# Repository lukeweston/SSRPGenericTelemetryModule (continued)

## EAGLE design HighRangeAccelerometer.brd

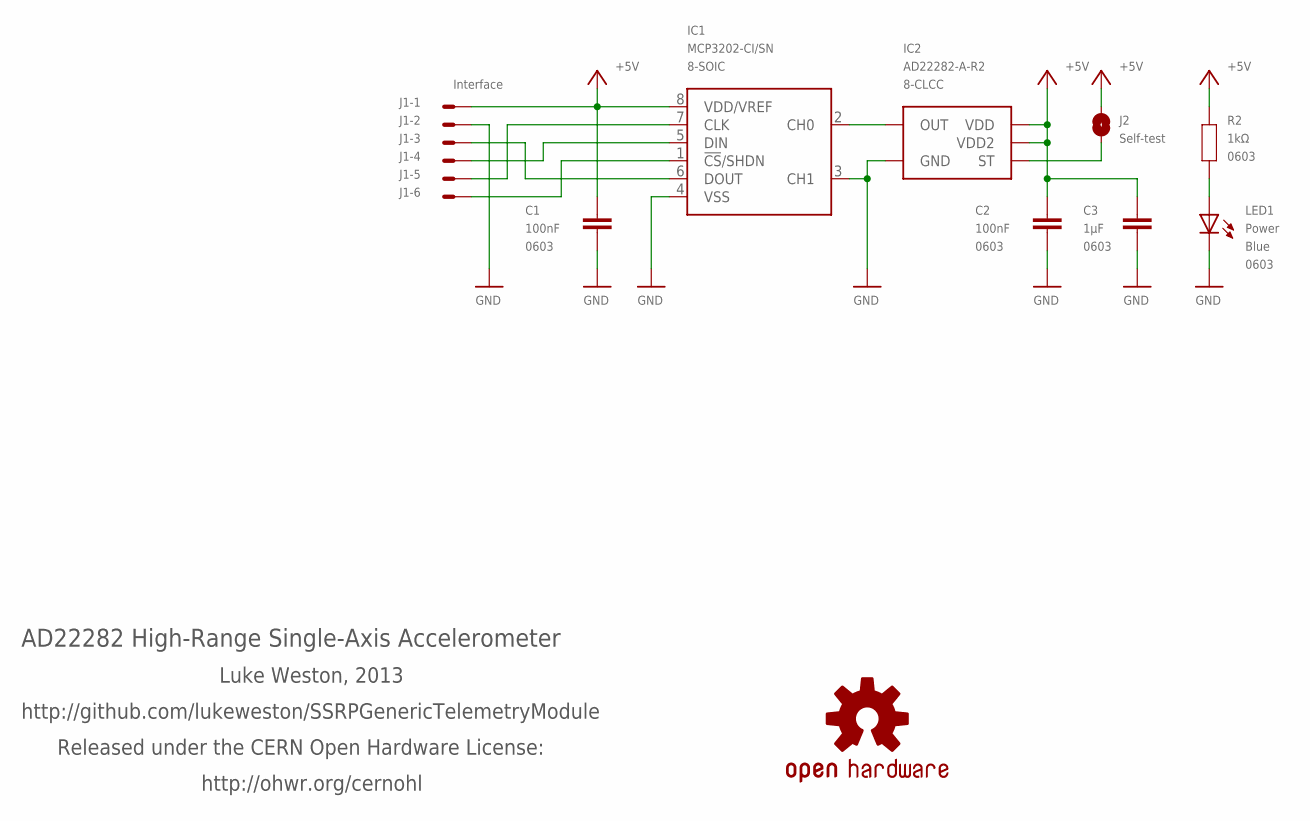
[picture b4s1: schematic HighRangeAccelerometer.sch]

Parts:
C1, C2: 100nF; 0603
C3: 1µF; 0603
IC1: MCP3202-CI/SN; SO-08
IC2: AD22282-A-R2; ADXL193
J1: Interface; 7395-06
J2: Self-test; SJ
LED1: Power; LED-0603
R2: 1kΩ; 0603
SY: OSHW-LOGOS; OSHW-LOGO-S

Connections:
+5V: C1.2, C2.2, C3.2, IC1.8 (VDD/VREF), IC2.P$7 (VDD), IC2.P$8 (VDD2), J1.1, J2.2, R2.2
GND: C1.1, C2.1, C3.1, IC1.3 (CH1), IC1.4 (VSS), IC2.P$3 (GND), J1.2, LED1.C
unnamed: IC1.2 (CH0), IC2.P$6 (OUT)
unnamed: LED1.A, R2.1
unnamed: IC1.6 (DOUT), J1.3
unnamed: IC1.5 (DIN), J1.4
unnamed: IC1.7 (CLK), J1.5
unnamed: IC1.1 (!CS!/SHDN), J1.6
unnamed: IC2.P$4 (ST), J2.1

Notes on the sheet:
AD22282 High-Range Single-Axis Accelerometer
Luke Weston, 2013
http://github.com/lukeweston/SSRPGenericTelemetryModule
Released under the CERN Open Hardware License:
http://ohwr.org/cernohl

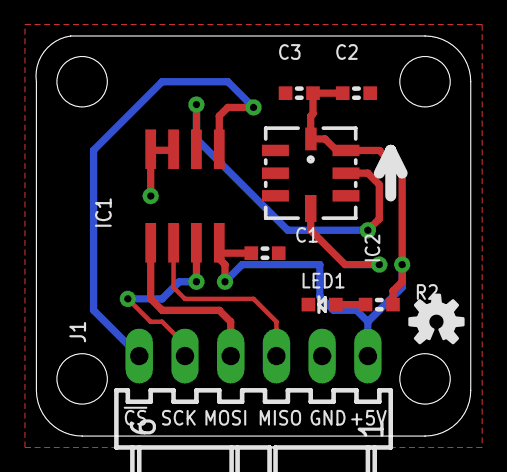
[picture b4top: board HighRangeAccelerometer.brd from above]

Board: 2 copper layers, 24.2 x 22.2 mm, 10 parts (1 on the bottom side), 9 nets.

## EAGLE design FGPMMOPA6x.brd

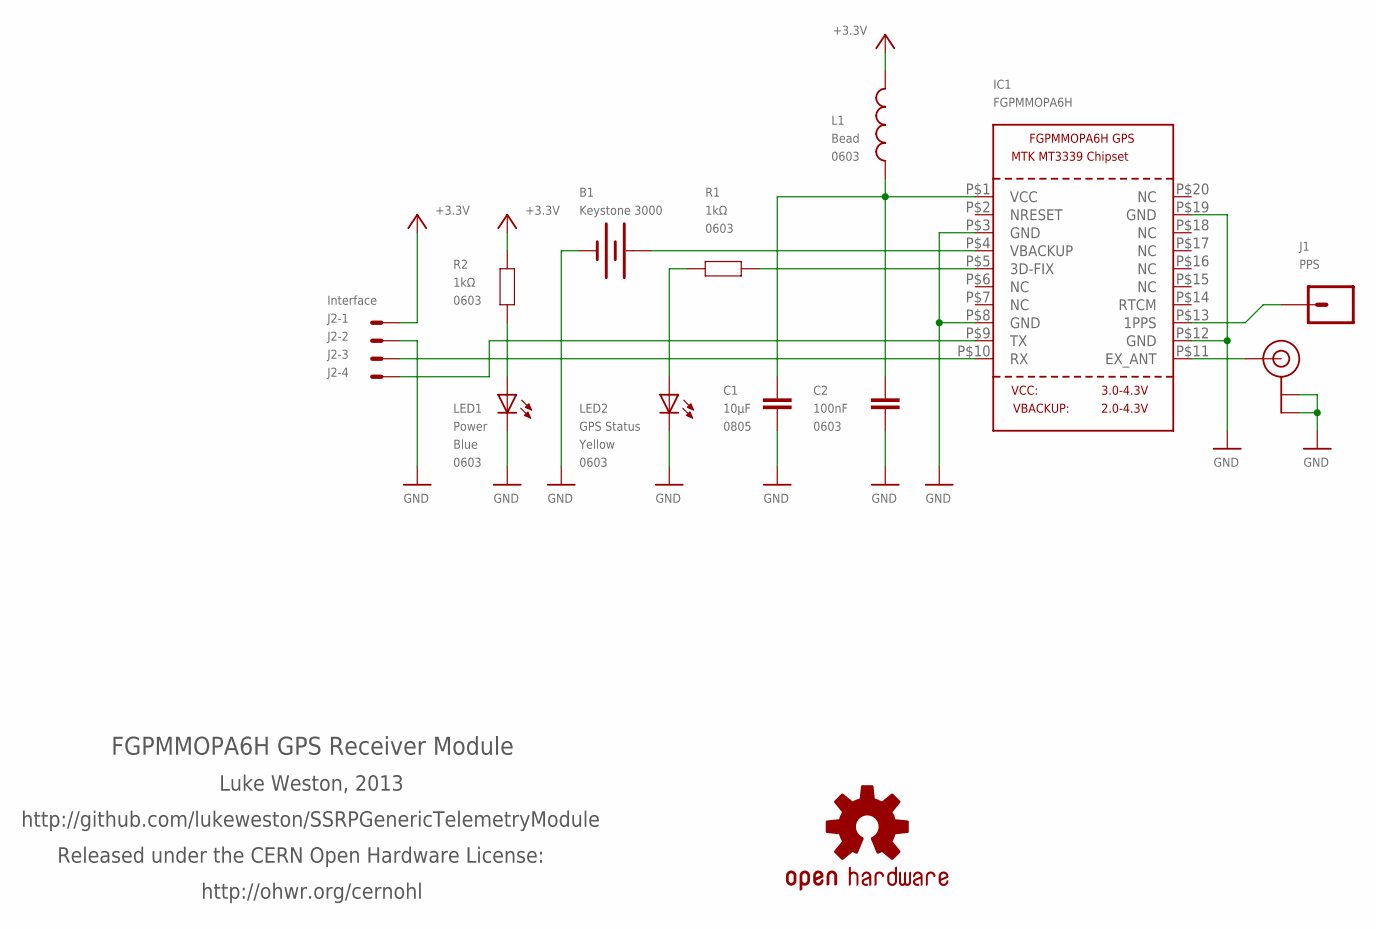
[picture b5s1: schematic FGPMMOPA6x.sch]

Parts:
B1: Keystone 3000; BATTCON_12MM
C1: 10µF; 0805
C2: 100nF; 0603
IC1: FGPMMOPA6H
J1: PPS; 1X01
J2: Interface; 7395-04
J3: U.FL
L1: Bead; 0603
LED1: Power; LED-0603
LED2: GPS Status; LED-0603
R1, R2: 1kΩ; 0603
SY2: OSHW-LOGOS; OSHW-LOGO-S

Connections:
+3V3: J2.1, L1.2, R2.2
GND: B1.GND (-), C1.1, C2.1, IC1.P$3 (GND), IC1.P$8 (GND), IC1.P$12 (GND), IC1.P$19 (GND), J2.2, J3.P$1 (GND), J3.P$2 (GND), LED1.C, LED2.C
unnamed: C1.2, C2.2, IC1.P$1 (VCC), L1.1
unnamed: B1.PWR@1 (+), IC1.P$4 (VBACKUP)
unnamed: IC1.P$5 (3D-FIX), R1.2
unnamed: IC1.P$9 (TX), J2.4
unnamed: IC1.P$10 (RX), J2.3
unnamed: IC1.P$13 (1PPS), J1.1
unnamed: IC1.P$11 (EX_ANT), J3.P$3 (SIGNAL)
unnamed: LED2.A, R1.1
unnamed: LED1.A, R2.1

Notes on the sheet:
FGPMMOPA6H GPS Receiver Module
Luke Weston, 2013
http://github.com/lukeweston/SSRPGenericTelemetryModule
Released under the CERN Open Hardware License:
http://ohwr.org/cernohl

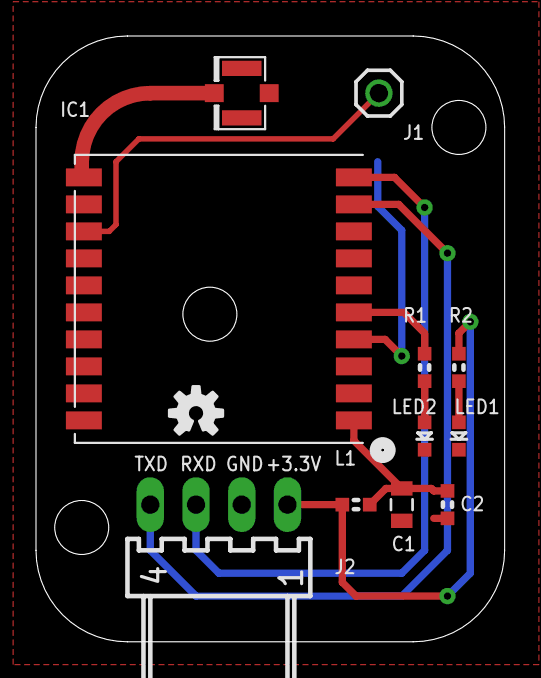
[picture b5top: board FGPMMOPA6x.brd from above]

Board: 2 copper layers, 26.0 x 33.7 mm, 13 parts (1 on the bottom side), 11 nets.

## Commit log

2013-02-19 added OEMV-1 CAN/UART/Power interface board
